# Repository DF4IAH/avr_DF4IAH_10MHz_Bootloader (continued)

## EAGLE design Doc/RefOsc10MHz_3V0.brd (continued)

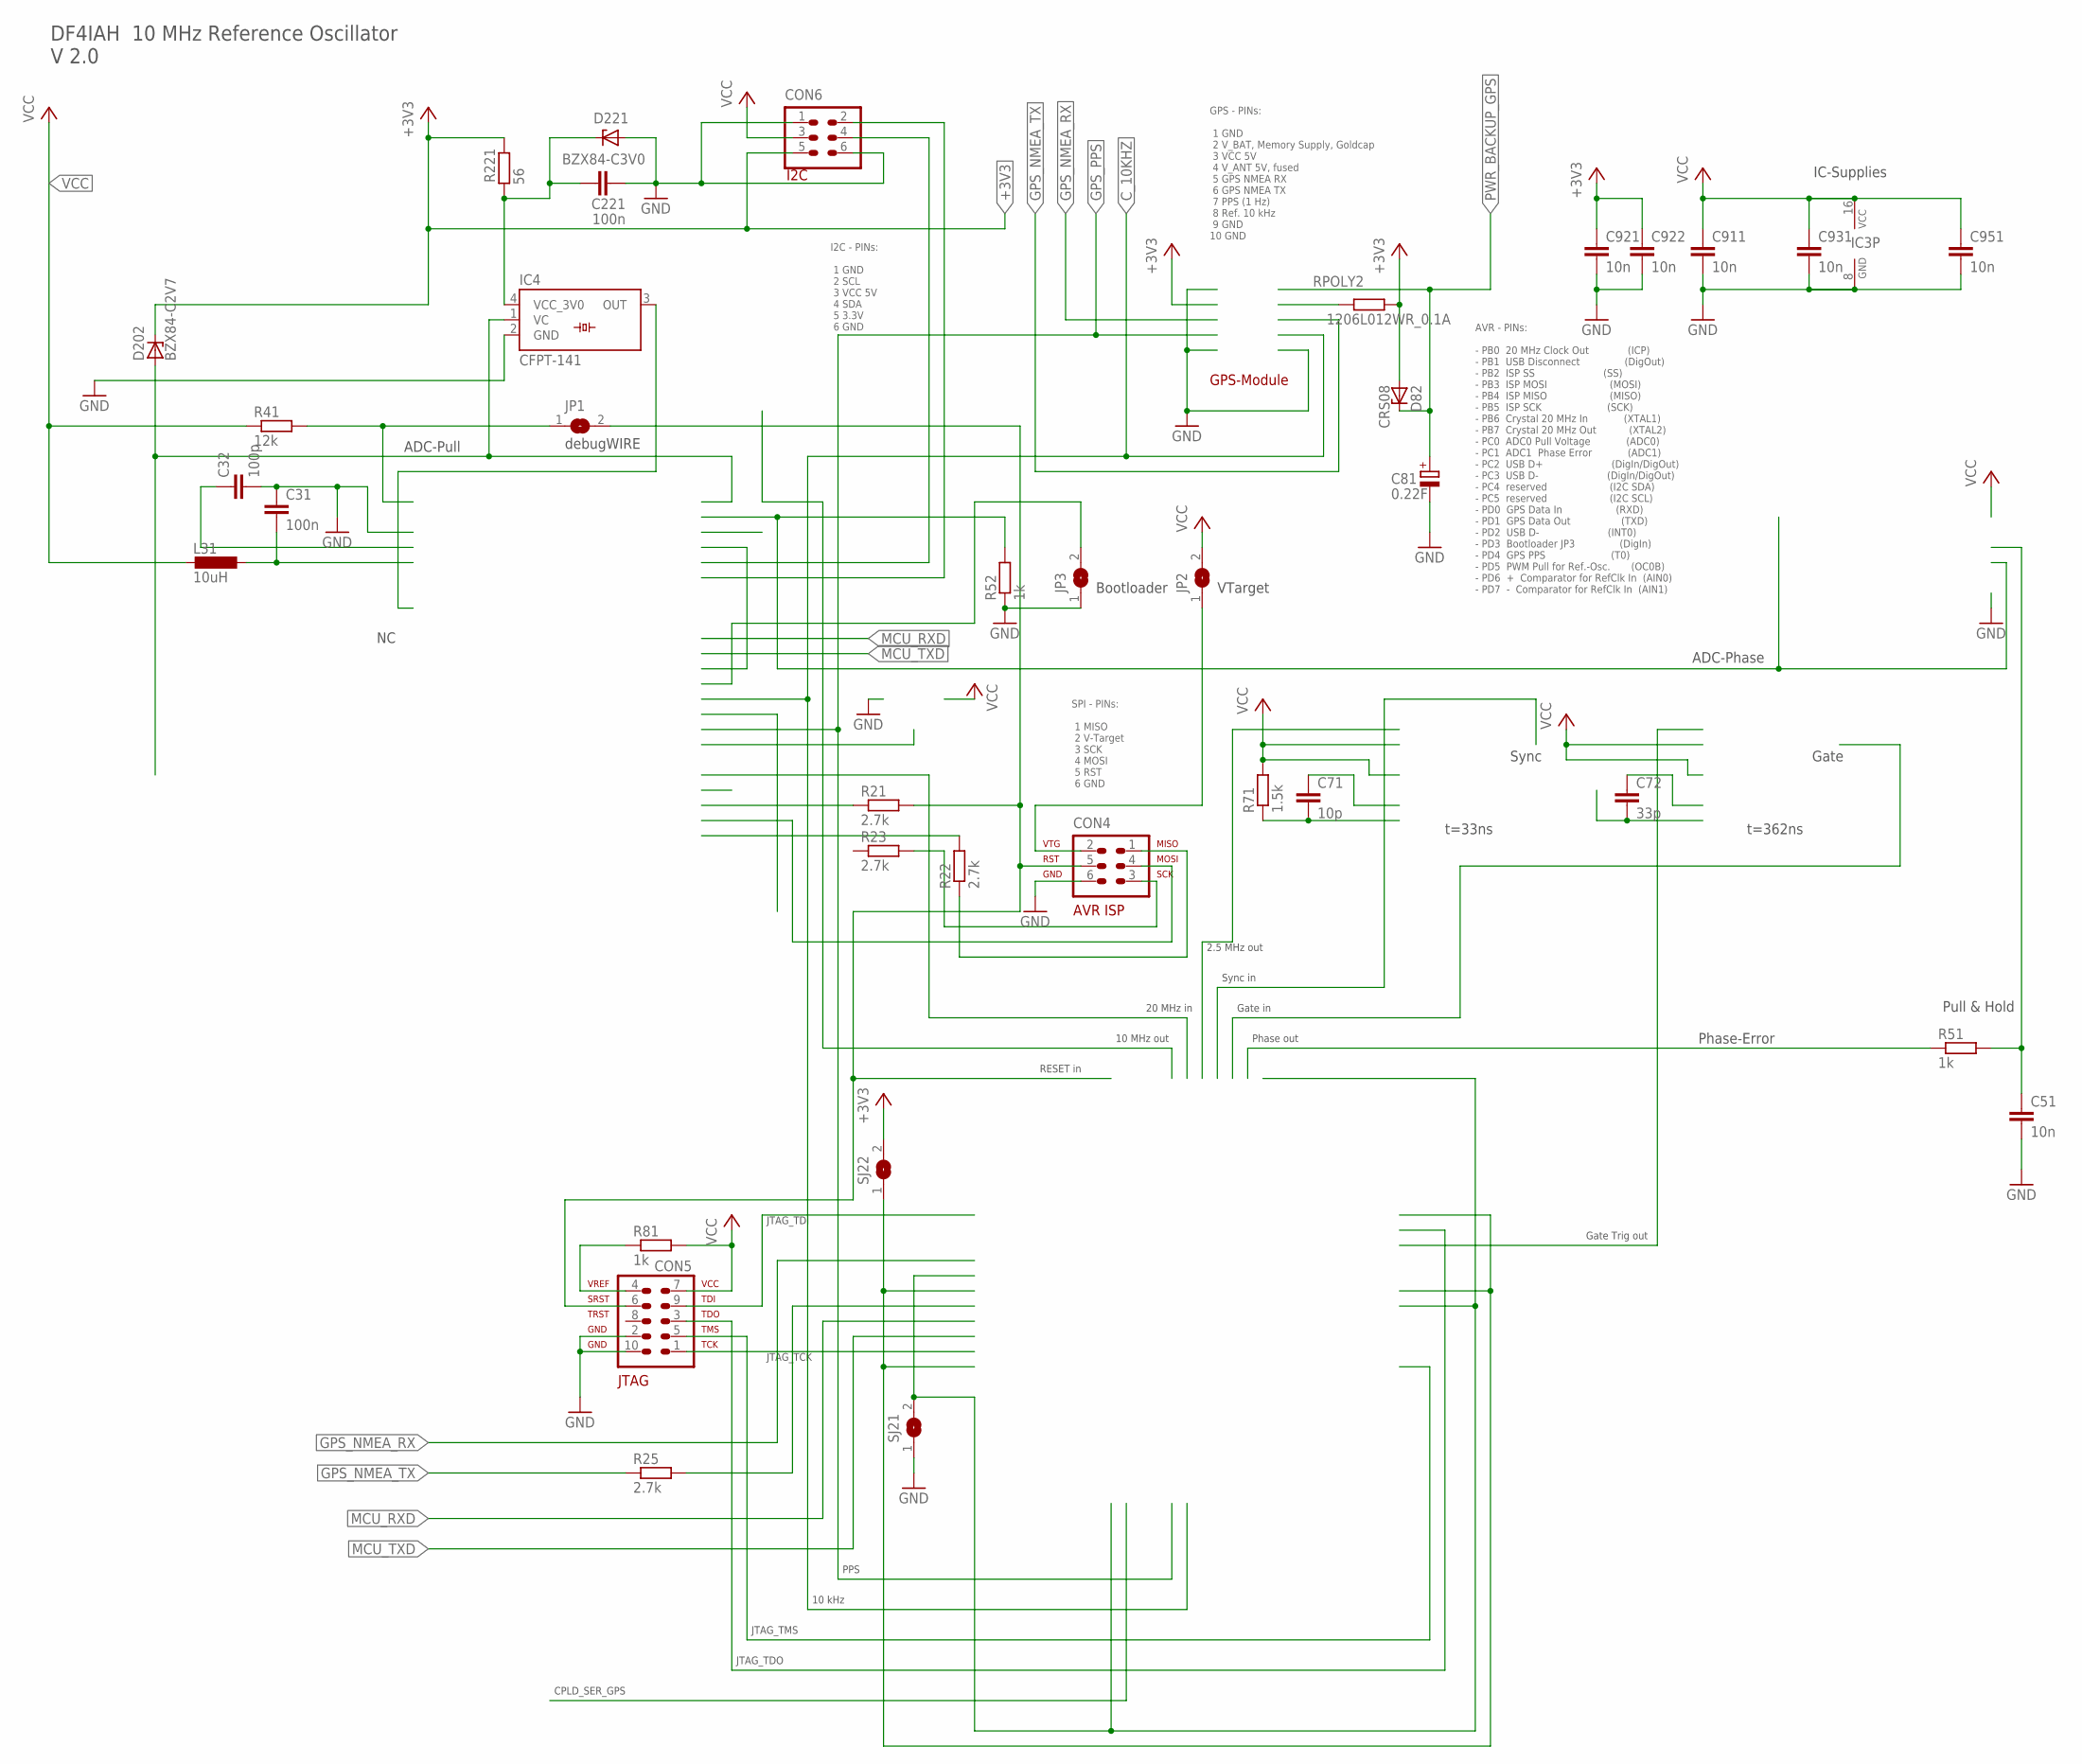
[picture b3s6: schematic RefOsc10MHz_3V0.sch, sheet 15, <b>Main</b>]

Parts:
C31, C221: 100n; C0805
C32: 100p; C0805
C51, C911, C921, C922, C931, C951: 10n; C0805
C71: 10p; C0805
C72: 33p; C0805
C81: 0.22F; PANASONIC_C
CON4: AVR-ISP-6SMD; 2X3SMD
CON5: AVR-JTAG-10SMD; 2X5SMD
CON6: HEADER-2X3SMD; 2X03SMD
D82: CRS08; SOT23
D202: BZX84-C2V7; TO236
D221: BZX84-C3V0; TO236
IC3: 74HCT221D; SO16
IC4: CFPT-141
JP1, JP2, JP3: SJW
L31: 10uH; L1812
R21, R22, R23, R25: 2.7k; R0805
R41: 12k; R0805
R51, R52, R81: 1k; R0805
R71: 1.5k; R0805
R221: 56; R0805
RPOLY2: 1206L012WR_0.1A; M1206
SJ21, SJ22: SJ

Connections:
+3V0: C221.1, D221.C, IC4.4 (VCC_3V0), R221.2
+3V3: C921.1, C922.1, CON6.5, D82.1 (A), D202.C, R221.1, RPOLY2.2, SJ22.2
ADC_PHASE: R52.2
ADC_PHASE_PULLHOLD: C51.1, R51.2
AREF: C32.1
AVCC: C31.2, L31.1
CPLD_GPS_NMEA_TX: R25.2
GND: C31.1, C32.2, C51.2, C81.-, C221.2, C911.2, C921.2, C922.2, C931.2, C951.2, CON4.6, CON5.2, CON5.10, CON6.1, CON6.6, D221.A, IC3.8 (GND), IC4.2 (GND), JP3.1, R52.1, SJ21.1; also elsewhere on the board
GND_SJ1: SJ21.2
GPS_ANT_PWR: RPOLY2.1
GPS_NMEA_TX: R25.1; also elsewhere on the board
INT1: JP3.2
ISP_MISO: CON4.1, R22.1
ISP_MOSI: CON4.4
ISP_SCK: CON4.3, R23.2
ISP_VTARGET: CON4.2, JP2.1
JTAG_SRST: CON4.5, CON5.6, JP1.2, R21.2
JTAG_TCK: CON5.1
JTAG_TDI: CON5.9
JTAG_TDO: CON5.3
JTAG_TMS: CON5.5
JTAG_VREF: CON5.4, R81.1
MISO: R22.2
unnamed: C71.2, R71.1
N_ADC_PULL: D202.A, IC4.1 (VC)
PHASE_ERROR: R51.1
PWR_BACKUP_GPS: C81.+, D82.3 (C); also elsewhere on the board
RESET: JP1.1, R41.2
SS: R21.1
TOSC1: IC4.3 (OUT)
VCC: C911.1, C931.1, C951.1, CON5.7, CON6.3, IC3.16 (VCC), JP2.2, L31.2, R41.1, R71.2, R81.2
VCC_3V3_SJ2: SJ22.1

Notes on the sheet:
VTarget
debugWIRE
AVR - PINs: - PB0 20 MHz Clock Out (ICP) - PB1 USB Disconnect (DigOut) - PB2 ISP SS (SS) - PB3 ISP MOSI (MOSI) - PB4 ISP MISO (MISO) - PB5 ISP SCK (SCK) - PB6 Crystal 20 MHz In (XTAL1) - PB7 Crystal 20 MHz Out (XTAL2) - PC0 ADC0 Pull Voltage (ADC0) - PC1 ADC1 Phase Error (ADC1) - PC2 USB D+ (DigIn/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
Bootloader
Phase-Error
Gate
GPS-Module
GPS - PINs: 1 GND 2 V_BAT, Memory Supply, Goldcap 3 VCC 5V 4 V_ANT 5V, fused 5 GPS NMEA RX 6 GPS NMEA TX 7 PPS (1 Hz) 8 Ref. 10 kHz 9 GND 10 GND
Pull & Hold
ADC-Phase
ADC-Pull
Sync
t=33ns
t=362ns
IC-Supplies
20 MHz in
10 MHz out
2.5 MHz out
DF4IAH 10 MHz Reference Oscillator V 2.0
SPI - PINs: 1 MISO 2 V-Target 3 SCK 4 MOSI 5 RST 6 GND
10 kHz
Sync in
Gate in
Phase out
PPS
RESET in
Gate Trig out
JTAG_TMS
JTAG_TDO
JTAG_TCK
JTAG_TDI
CPLD_SER_GPS
I2C - PINs: 1 GND 2 SCL 3 VCC 5V 4 SDA 5 3.3V 6 GND
I2C

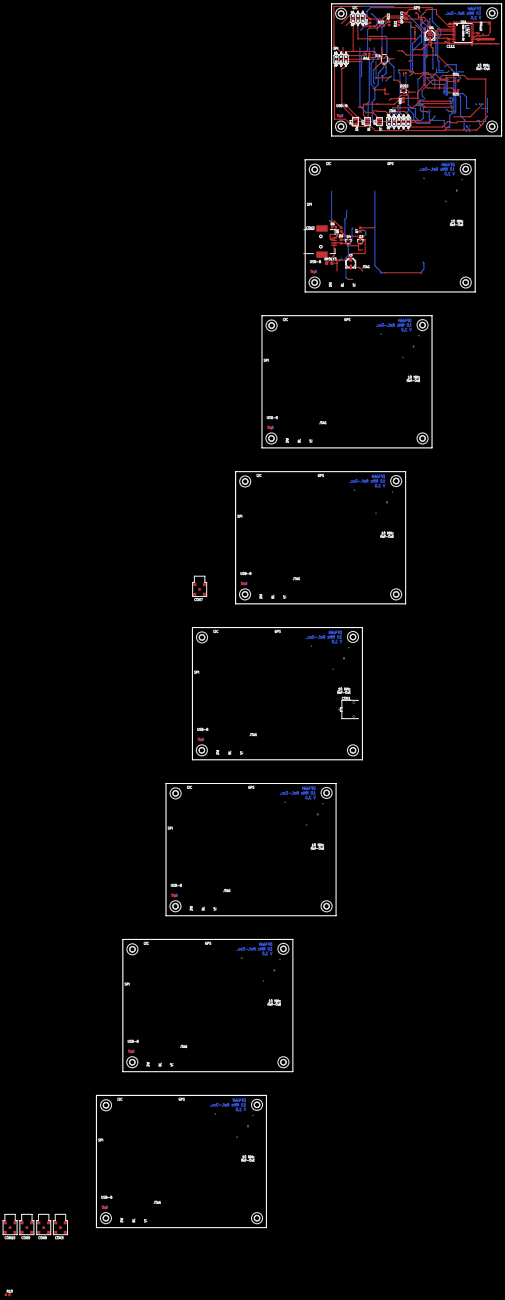
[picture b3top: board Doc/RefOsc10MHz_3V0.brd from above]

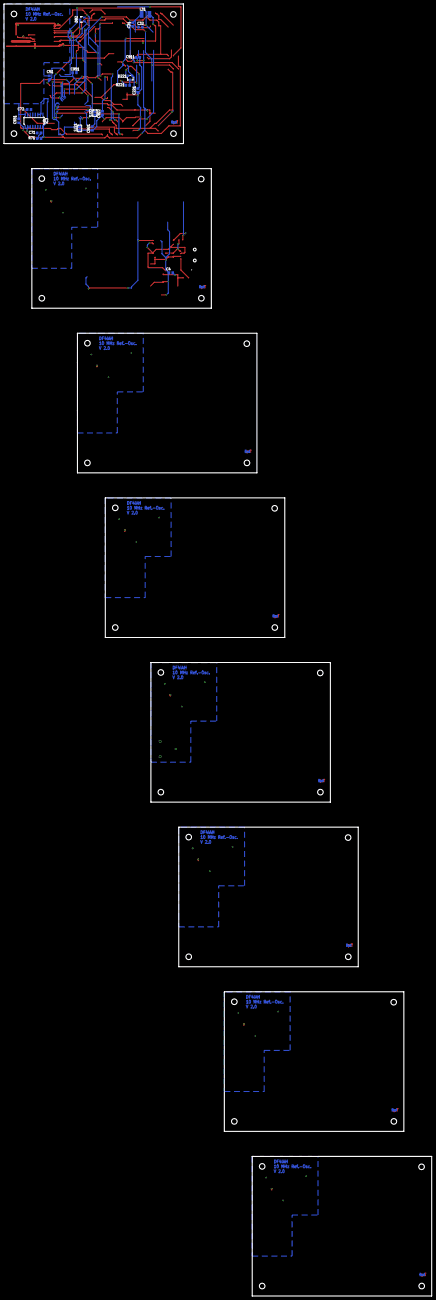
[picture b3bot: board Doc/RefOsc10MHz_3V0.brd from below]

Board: 2 copper layers, 214.5 x 647.9 mm, 89 parts (20 on the bottom side), 23 nets.

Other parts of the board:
U$1, U$2, U$3, U$4, U$5, U$6, U$7, U$8, U$9, U$10, U$11, U$12, U$13, U$14, U$15, U$16, U$17, U$18, U$19, U$20, U$21, U$22, U$23, U$24, U$25, U$26, U$27, U$28, U$29, U$30, U$31, U$32: 2,8

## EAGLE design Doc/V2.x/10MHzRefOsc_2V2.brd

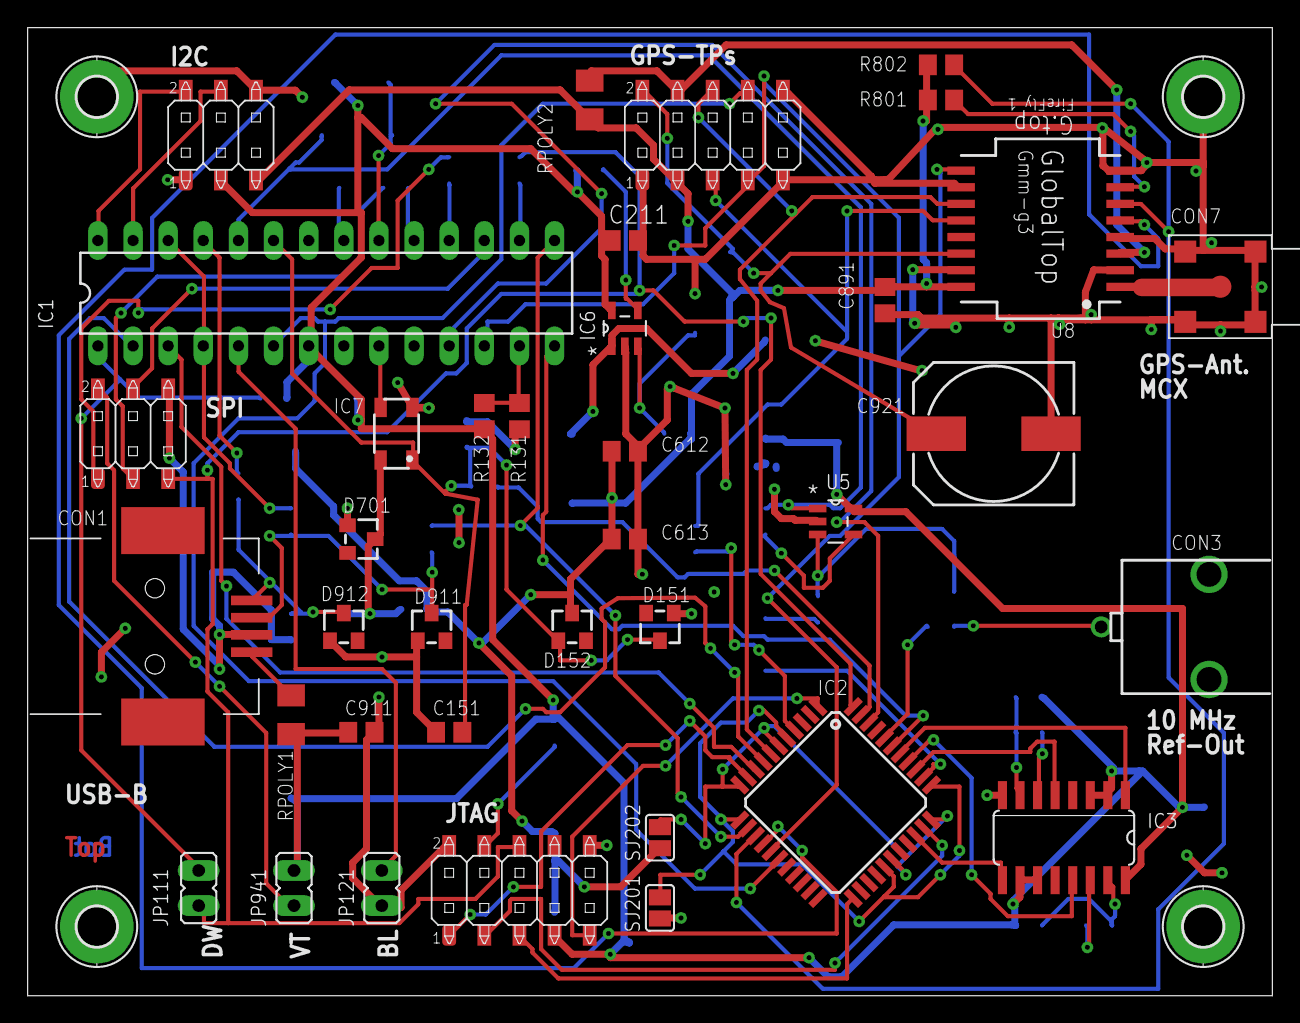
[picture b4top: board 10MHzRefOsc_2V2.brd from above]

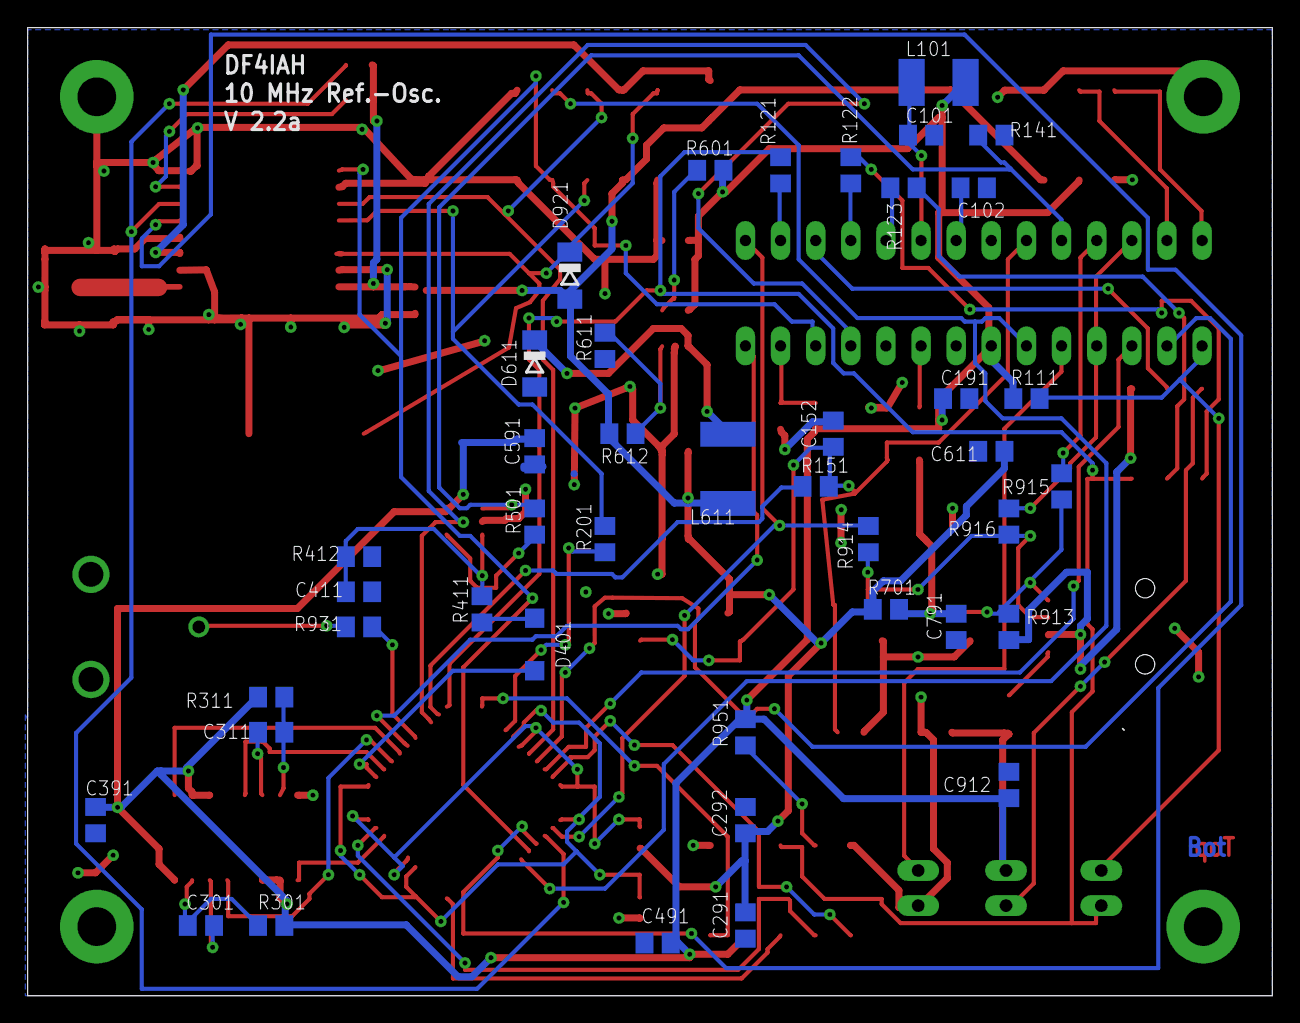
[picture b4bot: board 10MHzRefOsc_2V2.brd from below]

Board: 2 copper layers, 90.0 x 70.0 mm, 83 parts (42 on the bottom side), 69 nets.

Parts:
C101, C152, C191, C291, C292, C391, C491, C611, C791, C891, C912: 100n; C0805
C102, C411: 100p; C0805
C151: 10uF; C0805
C211, C612, C613: 22uF; C0805
C301: 0p; C0805
C311: 33p; C0805
C591: 10n; C0805
C911: 47uF; C0805
C921: 0.22F; 140CLH-1010
CON1: TYCO-AMP_USBUSB-B_SMT; TYCO-AMP_USB-B_SMT
CON2: HEADER-2X5SMD; 2X5SMD
CON3: SD-73100-0105; MOLEX_BNC-JACK-50R_SD-73100-0105
CON4: AVR-ISP-6SMD; 2X3SMD
CON5: AVR-JTAG-10SMD; 2X5SMD
CON6: HEADER-2X3SMD; 2X03SMD
CON7: MCX-J-P-X-RA-SM1
D151, D152, D911, D912: BZX84-C3V6; TO236
D401: 1N4448; SOD123
D611, D921: CRS08; SOD80C
D701: BZX84-C3V0; TO236
H901, H902, H903, H904: MOUNT-PAD-ROUND2.8; 2,8-PAD
IC1: ATmega328-P; DIL28-3
IC2: LC4032V_XXT44; TQFP44
IC3: 74HCT221D; SO16
IC6: LM2831YMF; SOT95P280X145-5N
IC7: CFPT-141
JP111, JP121, JP941: JP1
L101: 10uH; L1812
L611: 4.7uH; L5650M
R111: 12k; R0805
R121, R122, R123, R201, R411: 2.7k; R0805
R131, R151, R611: 15k; R0805
R132: 47k; R0805
R141: 1k; R0805
R301, R914: 1.5k; R0805
R311: 4.3k; R0805
R412: 2M; R0805
R501: 27; R0805
R601: 100k; R0805
R612: 68k; R0805
R701, R915, R916: 68; R0805
R801, R802: 10k; R0805
R913: 1M; R0805
R931: 51; R0805
R951: 150; R0805
RPOLY1: 1206L025YR_0.5A; M1206
RPOLY2: 1206L012WR_0.1A; M1206
SJ201, SJ202: SJ
U5: OPA354; SOT-23-5
U8: GLOBALTOP-FIREFLY1-GMM-G3

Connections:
+3V0: C791.1, D701.C, IC7.4, R701.2
+3V3: C291.1, C292.1, C611.1, C612.1, C613.1, CON2.3, CON6.5, D152.C, D921.A, L611.1, R612.1, R701.1, RPOLY2.2, SJ202.2
ADC_PHASE: IC1.24, R141.2, R501.1, U5.1
ADC_PHASE_SAMPLEHOLD: C411.1, R411.2, R412.2, U5.3
AIN1: IC1.13, R131.2, R132.1
AREF: C102.1, IC1.21
AVCC: C101.2, IC1.20, L101.1
CPLD_GPS_NMEA_RX: IC2.4, R201.2
C_2MHZ5: IC2.38, IC3.1
C_10KHZ: CON2.8, IC1.6, IC2.17
C_10MHZ: IC2.40, R931.1
C_20MHZ: IC1.14, IC2.39
EN: IC6.4, R601.2
FB: IC6.3, R611.2, R612.2
GATE_IN: IC2.36, IC3.5
GATE_TRIG_OUT: IC2.31, IC3.9
GND: C101.1, C102.2, C151.2, C152.2, C191.2, C211.2, C291.2, C292.2, C391.2, C411.2, C491.2, C591.2, C611.2, C612.2, C613.2, C791.2, C891.2, C911.2, C912.2, C921.-, CON1.4, CON2.1, CON2.9, CON2.10, CON3.2, CON3.3, CON4.6, CON5.2, CON5.10, CON6.1, CON6.6, CON7.2, CON7.3, CON7.4, CON7.5, D151.A, D611.A, D701.A, D911.A, D912.A, H901.B2,8, H902.B2,8, H903.B2,8, H904.B2,8, IC1.8, IC1.22, IC3.8, IC6.2, IC7.2, JP121.2, R131.1, R141.1, R412.1, R611.1, R913.1, SJ201.1, U5.2, U8.2, U8.4, U8.8, U8.10, U8.15
GND_SJ1: IC2.5, IC2.12, IC2.27, IC2.34, SJ201.2
GPS_2ND_RX: IC2.14, R802.1, U8.6
GPS_2ND_TX: IC2.15, U8.5
GPS_ANT_PWR: CON2.4, RPOLY2.1, U8.3
GPS_NMEA_RX: CON2.5, R201.1, U8.12
GPS_NMEA_TX: CON2.6, IC2.7, U8.11
GPS_NRESET: R801.1, U8.7
GPS_PPS: CON2.7, IC1.12, IC2.16, U8.9
GPS_VBACKUP: C921.+, CON2.2, D921.C, U8.14
INT1: IC1.5, JP121.1
ISP_MISO: CON4.1, R122.1
ISP_MOSI: CON4.4, IC1.17
ISP_SCK: CON4.3, R123.2
ISP_VTARGET: CON4.2, JP941.2
JTAG_SRST: CON4.5, CON5.6, IC2.44, JP111.2, R121.2
JTAG_TCK: CON5.1, IC2.10
JTAG_TDI: CON5.9, IC2.1
JTAG_TDO: CON5.3, IC2.32
JTAG_TMS: CON5.5, IC2.23
JTAG_VREF: CON5.4, R951.1
MCU_RXD: IC1.2, IC2.8
MCU_TXD: IC1.3, IC2.9
MISO: IC1.18, R122.2
unnamed: CON6.2, IC1.28
unnamed: CON7.1, U8.1
unnamed: CON6.4, IC1.27
unnamed: CON3.1, R931.2
unnamed: C311.2, IC3.7, R311.1
unnamed: C311.1, IC3.6
unnamed: C301.2, IC3.15, R301.1
unnamed: C301.1, IC3.14
N_ADC_PULL: C151.1, C152.1, D151.C, D152.A, IC1.23, IC7.1, R151.2
N_PWM_PULL_3V3: IC2.43, R151.1
N_PWM_PULL_5V0: IC1.11, IC2.42
N_USB_DISC: IC1.15, IC2.13, R914.2
N_USB_DMNS: IC1.4, IC1.26, R916.2
N_USB_DPLS: IC1.25, R915.2
PHASE_ERROR: D401.C, R411.1
PHASE_RSFF: D401.A, IC2.35
RESET: IC1.1, JP111.1, R111.2
SCK: IC1.19, R123.1
SS: IC1.16, R121.1
SW: D611.C, IC6.1, L611.2
SYNC_IN: IC2.37, IC3.13
TOSC1: IC1.9, IC7.3
U5_FB: R501.2, U5.4
USB_D_MIN: CON1.2, D911.C, R914.1, R916.1
USB_D_PLS: CON1.3, D912.C, R913.2, R915.1
USB_PWR: CON1.1, RPOLY1.1
VCC: C191.1, C211.1, C391.1, C491.1, C591.1, C911.1, C912.1, CON5.7, CON6.3, IC1.7, IC3.2, IC3.3, IC3.10, IC3.11, IC3.16, IC6.5, JP941.1, L101.2, R111.1, R132.2, R301.2, R311.2, R601.1, R951.2, RPOLY1.2, U5.5
VCC_3V3: C891.1, R801.2, R802.2, U8.16
VCC_3V3_SJ2: IC2.6, IC2.11, IC2.28, IC2.33, SJ202.1

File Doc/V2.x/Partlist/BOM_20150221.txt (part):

Stückliste exportiert aus /Users/espero/Documents/eagle/RefOsc10MHz/RefOsc10MHz_2V1.sch am 21.02.15 18:30

Qty Value                 Device                           Package                          Parts                                                            Description                                           MF                     MPN            OC_FARNELL OC_NEWARK PACKAGE  SUPPLIER              
2                         SJ                               SJ                               SJ201, SJ202                                                     SMD solder JUMPER                                                                                                                               
3                         SJW                              SJW                              JP111, JP121, JP941                                              SMD solder JUMPER                                                                                                                               
1   0.22F                 CPOL-EU140CLH-1010               140CLH-1010                      C921                                                             POLARIZED CAPACITOR, European symbol                                                                                                            
1   0p                    C-EUC0805                        C0805                            C301                                                             CAPACITOR, European symbol                                                                                                                      
2   1.5k                  R-EU_R0805                       R0805                            R301, R914                                                       RESISTOR, European symbol                                                                                                                       
1   100k                  R-EU_R0805                       R0805                            R601                                                             RESISTOR, European symbol                                                                                                                       
11  100n                  C-EUC0805                        C0805                            C101, C152, C191, C291, C292, C391, C491, C611, C791, C891, C912 CAPACITOR, European symbol                                                                                                                      
2   100p                  C-EUC0805                        C0805                            C102, C411                                                       CAPACITOR, European symbol                                                                                                                      
1   10k                   R-EU_R0805                       R0805                            R611                                                             RESISTOR, European symbol                                                                                                                       
1   10n                   C-EUC0805                        C0805                            C591                                                             CAPACITOR, European symbol                                                                                                                      
1   10uF                  CPOL-EUB                         PANASONIC_B                      C151                                                             POLARIZED CAPACITOR, European symbol                                                                                                            
1   10uH                  L-EUL1812                        L1812                            L101                                                             INDUCTOR, European symbol                                                                                                                       
1   1206L012WR_0.1A       R-EU_M1206                       M1206                            RPOLY2                                                           RESISTOR, European symbol                                                                                                                       
1   1206L025YR_0.5A       R-EU_M1206                       M1206                            RPOLY1                                                           RESISTOR, European symbol                                                                                                                       
1   12k                   R-EU_R0805                       R0805                            R111                                                             RESISTOR, European symbol                                                                                                                       
1   150                   R-EU_R0805                       R0805                            R951                                                             RESISTOR, European symbol                                                                                                                       
2   15k                   R-EU_R0805                       R0805                            R131, R151                                                       RESISTOR, European symbol                                                                                                                       
1   1M                    R-EU_R0805                       R0805                            R913                                                             RESISTOR, European symbol                                                                                                                       
1   1N4448                DIODE-SOD123                     SOD123                           D401                                                             DIODE                                                                                                                                           
1   1k                    R-EU_R0805                       R0805                            R141                                                             RESISTOR, European symbol                                                                                                                       
5   2.7k                  R-EU_R0805                       R0805                            R121, R122, R123, R201, R411                                     RESISTOR, European symbol                                                                                                                       
3   22uF                  CPOL-EUA/3216-18W                A/3216-18W                       C211, C612, C613                                                 POLARIZED CAPACITOR, European symbol                                                                                                            
1   27                    R-EU_R0805                       R0805                            R501                                                             RESISTOR, European symbol                                                                                                                       
1   2M                    R-EU_R0805                       R0805                            R412                                                             RESISTOR, European symbol                                                                                                                       
1   33p                   C-EUC0805                        C0805                            C311                                                             CAPACITOR, European symbol                                                                                                                      
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
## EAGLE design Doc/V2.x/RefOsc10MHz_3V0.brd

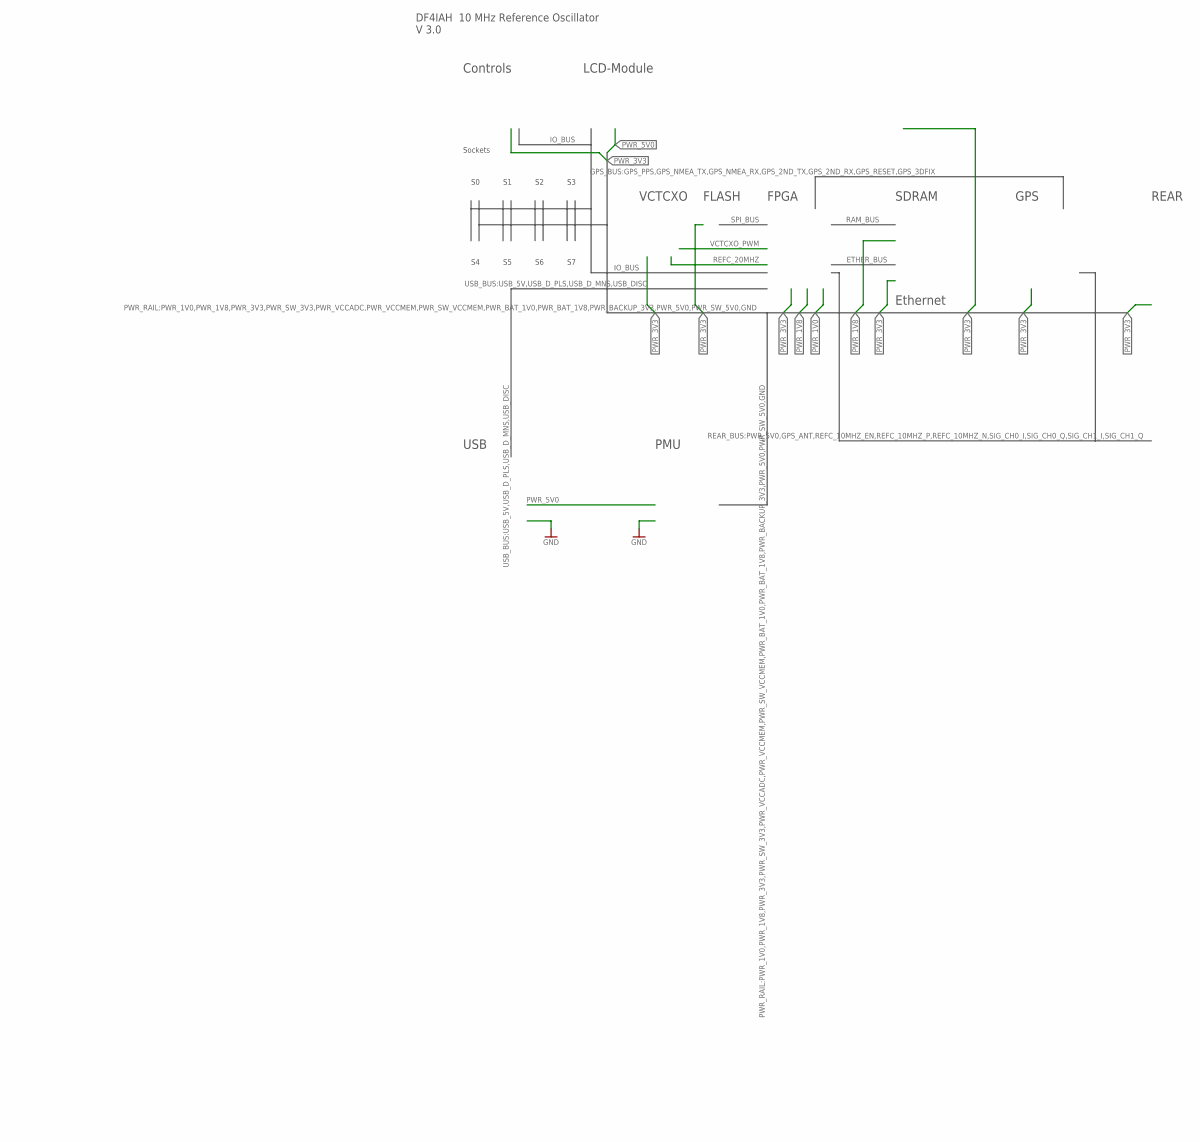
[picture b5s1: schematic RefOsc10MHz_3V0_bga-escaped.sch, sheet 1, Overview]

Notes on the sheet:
VCTCXO
FPGA
GPS
REAR
LCD-Module
Controls
USB
PMU
Sockets
SDRAM
Ethernet
FLASH
DF4IAH 10 MHz Reference Oscillator V 3.0

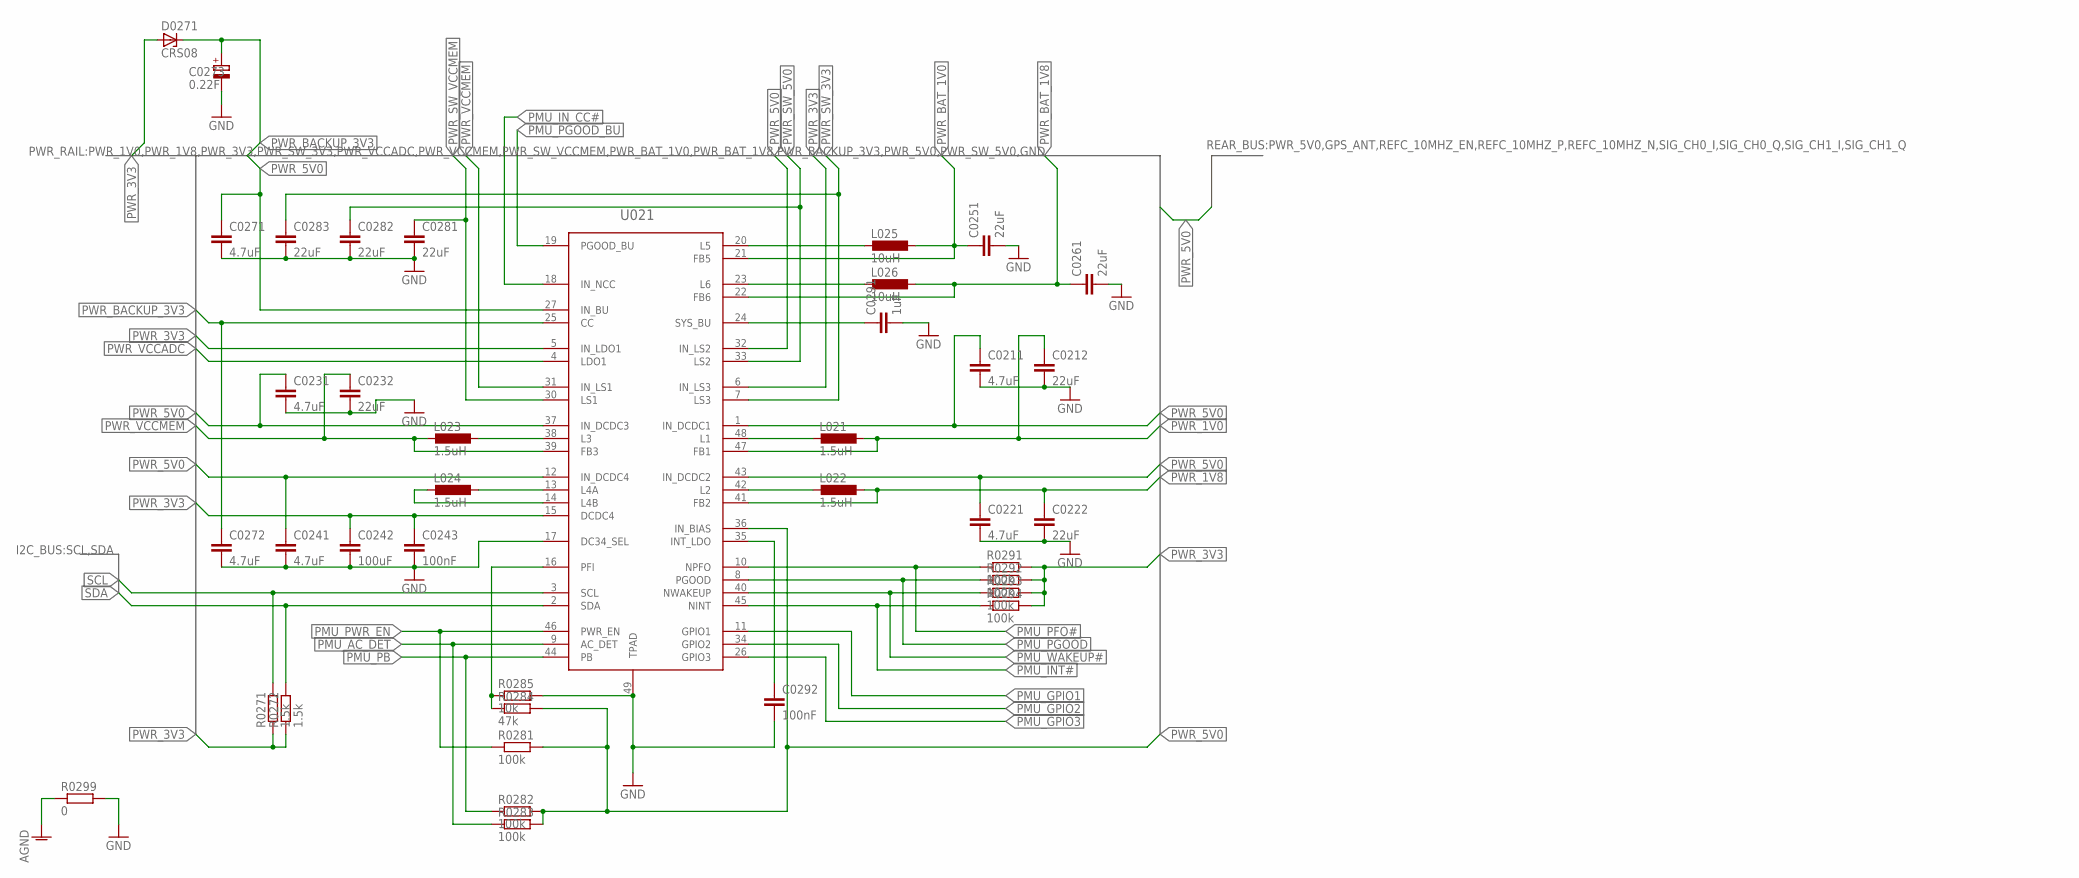
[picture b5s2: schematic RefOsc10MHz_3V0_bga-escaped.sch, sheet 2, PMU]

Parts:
C0211, C0221, C0231, C0241, C0271, C0272: 4.7uF; C0805
C0212, C0222, C0232, C0251, C0261, C0281, C0282, C0283: 22uF; C0805
C0242: 100uF; C0805
C0243, C0292: 100nF; C0805
C0273: 0.22F; PANASONIC_C
C0291: 1uF; C0805
D0271: CRS08; SOT23
L021, L022, L023, L024: 1.5uH; L1812
L025, L026: 10uH; L1812
R0271, R0272: 1.5k; R0603
R0281, R0282, R0283, R0291, R0292, R0293, R0294: 100k; R0603
R0284: 47k; R0603
R0285: 10k; R0603
R0299: 0; R0805
U021: TPS65218; QFP50P900X900X120-49N2

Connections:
AGND: R0299.1; also elsewhere on the board
GND: C0211.2, C0212.2, C0221.2, C0222.2, C0231.2, C0232.2, C0241.2, C0242.2, C0243.2, C0251.2, C0261.2, C0271.2, C0272.2, C0273.-, C0281.2, C0282.2, C0283.2, C0291.2, C0292.2, R0285.2, R0299.2, U021.17 (DC34_SEL), U021.49 (TPAD); also elsewhere on the board
L1: L021.2, U021.48 (L1)
L2: L022.2, U021.42 (L2)
L3: L023.1, U021.38 (L3)
L4A: L024.1, U021.13 (L4A)
L4B: L024.2, U021.14 (L4B)
L5: L025.2, U021.20 (L5)
L6: L026.2, U021.23 (L6)
unnamed: C0292.1, U021.35 (INT_LDO)
unnamed: R0284.1, R0285.1, U021.16 (PFI)
PMU_AC_DET: R0283.1, U021.9 (AC_DET)
PMU_GPIO1: U021.11 (GPIO1); also elsewhere on the board
PMU_GPIO2: U021.34 (GPIO2); also elsewhere on the board
PMU_GPIO3: U021.26 (GPIO3); also elsewhere on the board
PMU_INT#: R0294.1, U021.45 (NINT); also elsewhere on the board
PMU_IN_CC#: U021.18 (IN_NCC); also elsewhere on the board
PMU_PB: R0282.1, U021.44 (PB)
PMU_PFO#: R0291.1, U021.10 (NPFO); also elsewhere on the board
PMU_PGOOD: R0292.1, U021.8 (PGOOD); also elsewhere on the board
PMU_PGOOD_BU: U021.19 (PGOOD_BU); also elsewhere on the board
PMU_PWR_EN: R0281.1, U021.46 (PWR_EN); also elsewhere on the board
PMU_WAKEUP#: R0293.1, U021.40 (NWAKEUP); also elsewhere on the board
PWR_1V0: C0212.1, L021.1, U021.47 (FB1); also elsewhere on the board
PWR_1V8: C0222.1, L022.1, U021.41 (FB2); also elsewhere on the board
PWR_3V3: C0242.1, C0243.1, D0271.1 (A), R0271.1, R0272.1, R0291.2, R0292.2, R0293.2, R0294.2, U021.5 (IN_LDO1), U021.6 (IN_LS3), U021.15 (DCDC4); also elsewhere on the board
PWR_5V0: C0211.1, C0221.1, C0231.1, C0241.1, C0271.1, R0281.2, R0282.2, R0283.2, R0284.2, U021.1 (IN_DCDC1), U021.12 (IN_DCDC4), U021.27 (IN_BU), U021.32 (IN_LS2), U021.36 (IN_BIAS), U021.37 (IN_DCDC3), U021.43 (IN_DCDC2); also elsewhere on the board
PWR_BACKUP_3V3: C0272.1, C0273.+, D0271.3 (C), U021.25 (CC); also elsewhere on the board
PWR_BAT_1V0: C0251.1, L025.1, U021.21 (FB5)
PWR_BAT_1V8: C0261.1, L026.1, U021.22 (FB6); also elsewhere on the board
PWR_SW_3V3: C0283.1, U021.7 (LS3)
PWR_SW_5V0: C0282.1, U021.33 (LS2)
PWR_SW_VCCMEM: C0281.1, U021.30 (LS1)
PWR_VCCADC: U021.4 (LDO1); also elsewhere on the board
PWR_VCCMEM: C0232.1, L023.2, U021.31 (IN_LS1), U021.39 (FB3)
SCL: R0271.2, U021.3 (SCL); also elsewhere on the board
SDA: R0272.2, U021.2 (SDA); also elsewhere on the board
SYS_BU: C0291.1, U021.24 (SYS_BU)

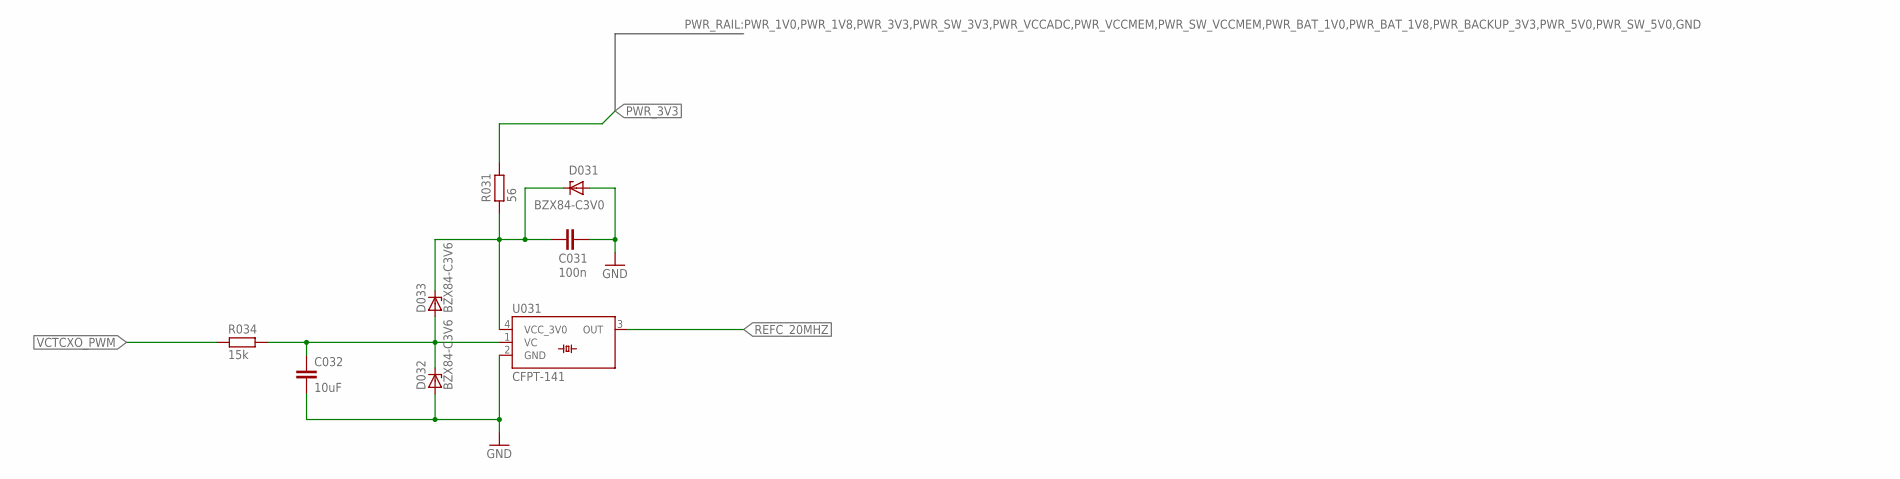
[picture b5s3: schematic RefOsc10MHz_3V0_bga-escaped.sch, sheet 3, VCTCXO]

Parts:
C031: 100n; C0805
C032: 10uF; C0805
D031: BZX84-C3V0; TO236
D032, D033: BZX84-C3V6; TO236
R031: 56; R0805
R034: 15k; R0603
U031: CFPT-141

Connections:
GND: C031.2, C032.2, D031.A, D032.A, U031.2 (GND); also elsewhere on the board
PWR_3V3: R031.1; also elsewhere on the board
PWR_VCTCXO_3V0: C031.1, D031.C, D033.C, R031.2, U031.4 (VCC_3V0)
REFC_20MHZ: U031.3 (OUT); also elsewhere on the board
VCTCXO_PWM: R034.2; also elsewhere on the board
VCTCXO_VC_IN: C032.1, D032.C, D033.A, R034.1, U031.1 (VC)
